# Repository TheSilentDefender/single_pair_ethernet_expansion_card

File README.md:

# single_pair_ethernet_expansion_card

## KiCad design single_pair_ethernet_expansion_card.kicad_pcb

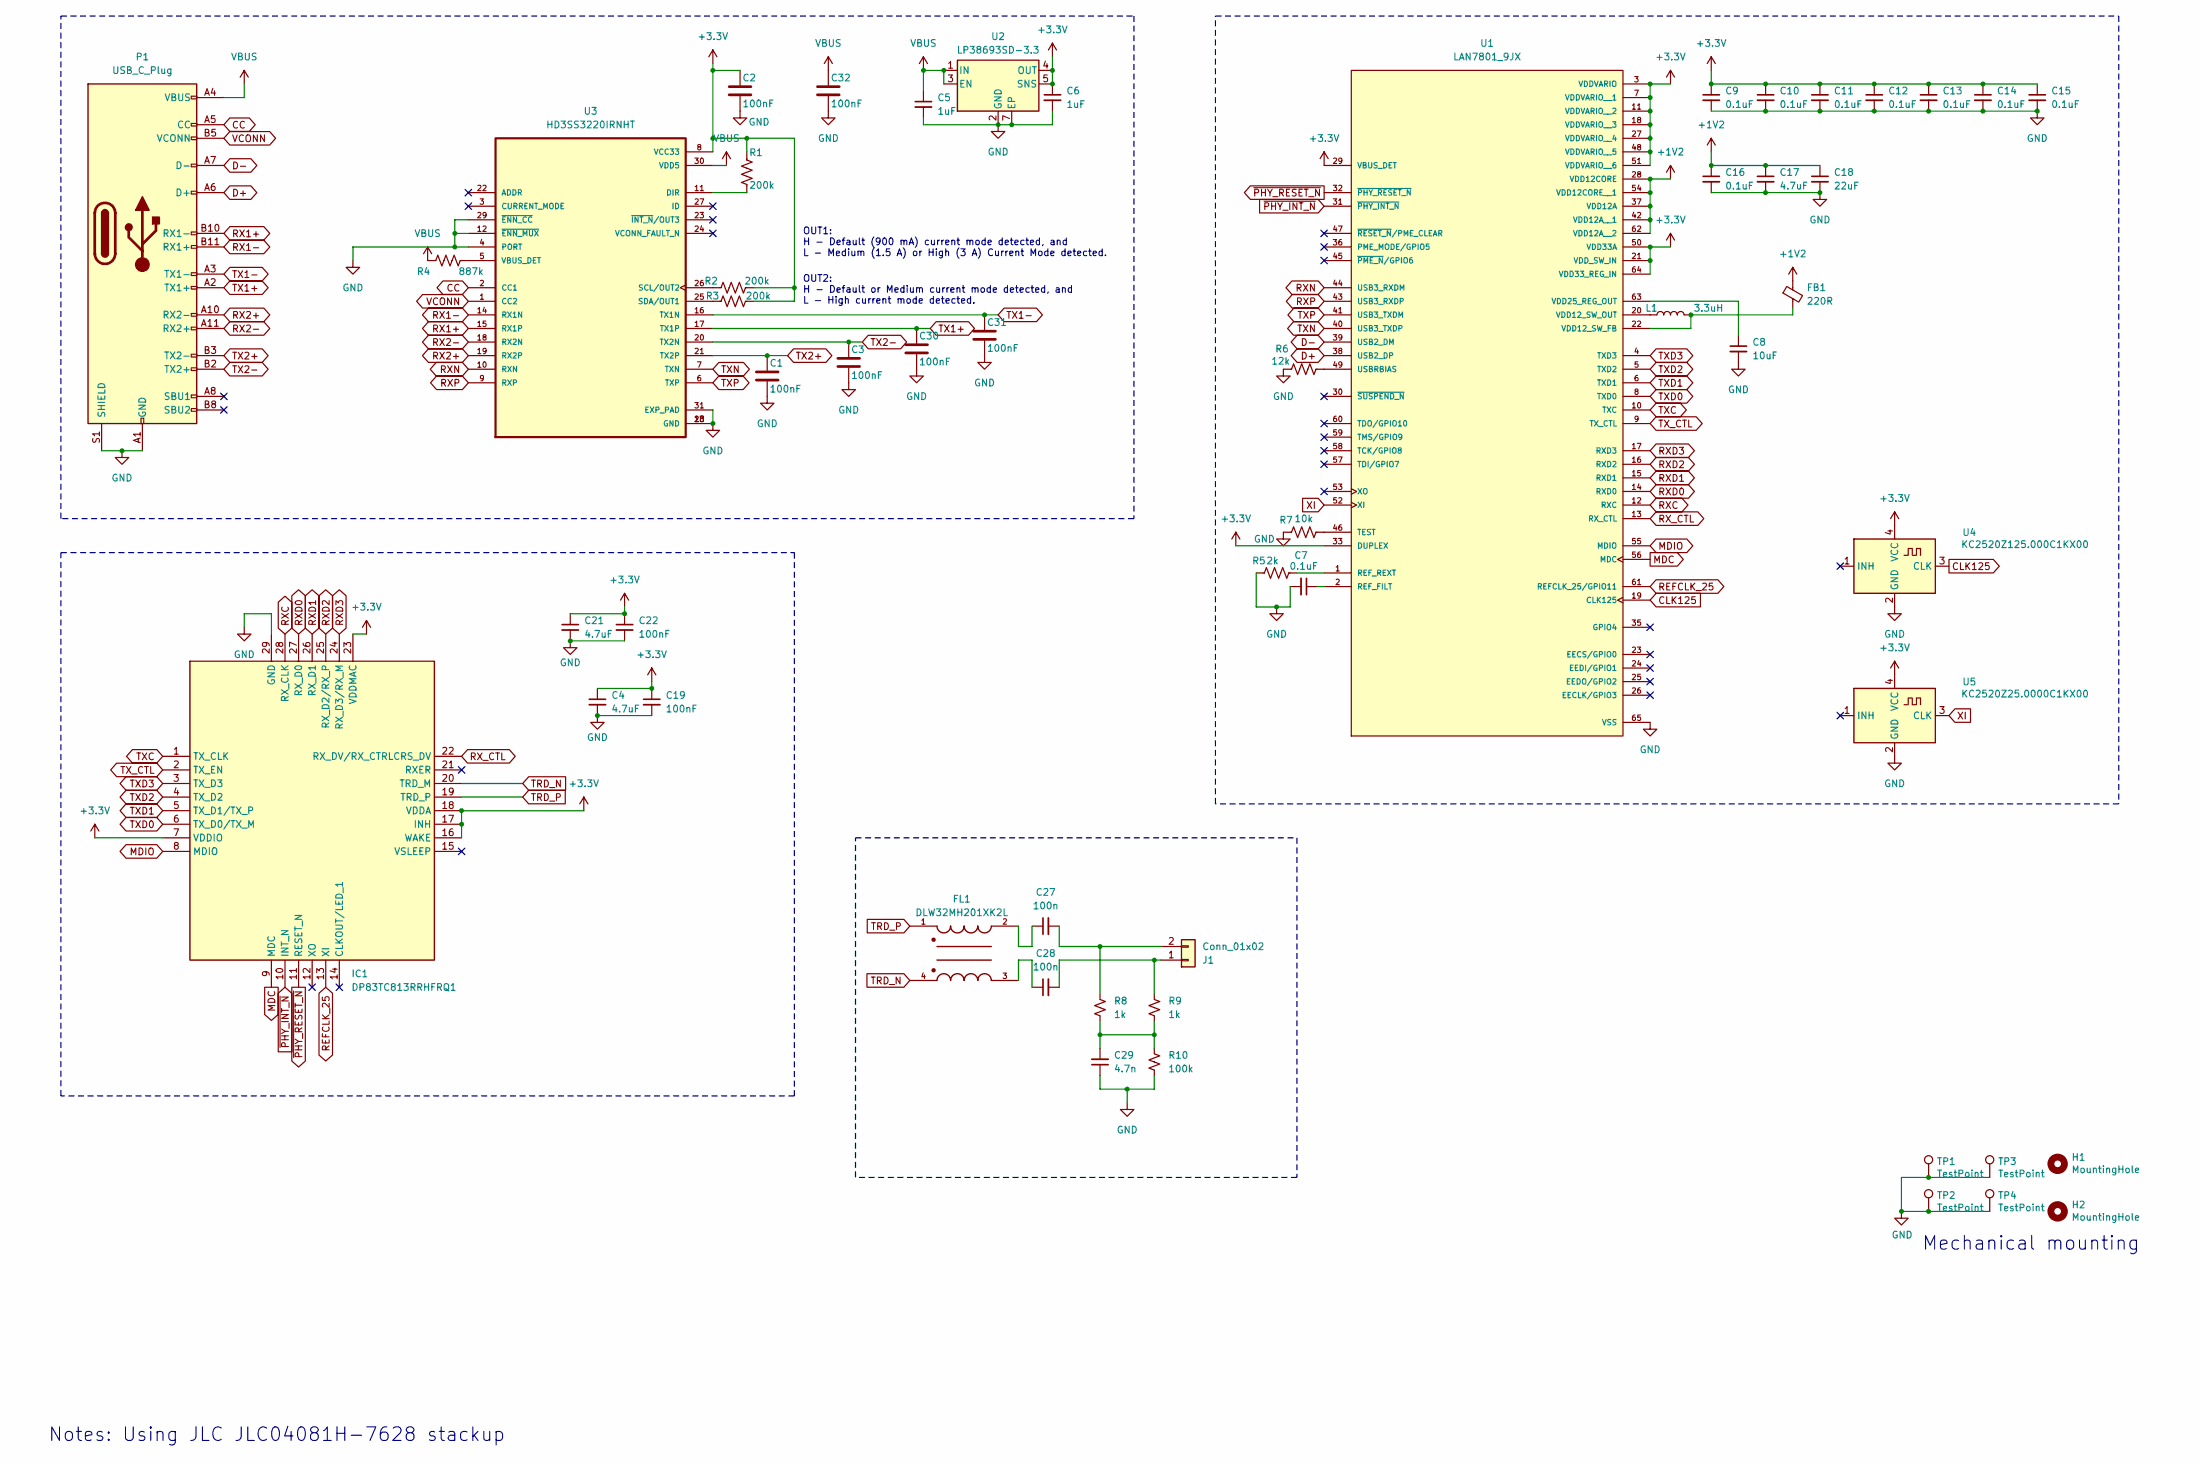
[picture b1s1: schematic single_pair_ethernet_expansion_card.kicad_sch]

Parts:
C1, C2, C3, C30, C31, C32: CC0402KRX5R7BB105; C_0201_0603Metric
C4, C17, C21: 4.7uF; C_0201_0603Metric
C5, C6: 1uF; C_0201_0603Metric
C7, C9, C10, C11, C12, C13, C14, C15, C16: 0.1uF; C_0201_0603Metric
C8: 10uF; C_0201_0603Metric
C18: 22uF; C_0201_0603Metric
C19, C22: 100nF; C_0201_0603Metric
C27, C28: 100n; C_0201_0603Metric
C29: 4.7n; C_0201_0603Metric
FB1: 220R; L_0201_0603Metric
FL1: DLW32MH201XK2L; FIL_DLW32MH201XK2L; PARTREV N/A
H1, H2: MountingHole; MountingHole_2.2mm_M2
IC1: DP83TC813RRHFRQ1; QFN50P400X500X100-29N-D; Mouser Part Number 595-DP83TC813RRHFRQ1
J1: Conn_01x02; JST_SH_SM02B-SRSS-TB_1x02-1MP_P1.00mm_Horizontal
L1: 3.3uH; L_0805_2012Metric
P1: USB_C_Plug; USB_C_Plug_Molex_105444
R1, R2, R3: RC0402JR-07200KL; R_0402_1005Metric
R4: RC0402FR-07887KL; R_0402_1005Metric
R5: 2k; R_0402_1005Metric
R6: 12k; R_0402_1005Metric
R7: 10k; R_0402_1005Metric
R8, R9: 1k; R_0402_1005Metric
R10: 100k; R_0402_1005Metric
TP1, TP2, TP3, TP4: TestPoint; TestPoint_Pad_1.5x1.5mm
U1: LAN7801_9JX; QFN50P900X900X100-65N_LAN7801_9JX; PARTREV DS00002123F
U2: LP38693SD-3.3; WSON-6-1EP_3x3mm_P0.95mm
U3: HD3SS3220IRNHT; QFN40P450X250X80-31N120X320; PART_REV C
U4: KC2520Z125.000C1KX00; Oscillator_SMD_Kyocera_KC2520Z-4Pin_2.5x2.0mm
U5: KC2520Z25.0000C1KX00; Oscillator_SMD_Kyocera_KC2520Z-4Pin_2.5x2.0mm

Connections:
+1V2: C16.1, C17.1, C18.1, FB1.1, U1.28 (VDD12CORE), U1.37 (VDD12A), U1.42 (VDD12A__1), U1.54 (VDD12CORE__1), U1.62 (VDD12A__2)
+3.3V: C2.1, C4.1, C6.1, C9.1, C10.1, C11.1, C12.1, C13.1, C14.1, C15.1, C19.1, C21.1, C22.1, IC1.7 (VDDIO), IC1.16 (WAKE), IC1.17 (INH), IC1.18 (VDDA), IC1.23 (VDDMAC), R1.1, R2.2, R3.2, U1.3 (VDDVARIO), U1.7 (VDDVARIO__1), U1.11 (VDDVARIO__2), U1.18 (VDDVARIO__3), U1.21 (VDD_SW_IN), U1.27 (VDDVARIO__4), U1.29 (VBUS_DET), U1.33 (DUPLEX), U1.48 (VDDVARIO__5), U1.50 (VDD33A), U1.51 (VDDVARIO__6), U1.64 (VDD33_REG_IN), U2.4 (OUT), U2.5 (SNS), U3.8 (VCC33), U4.4 (VCC), U5.4 (VCC)
CC: P1.A5 (CC), U3.2 (CC1)
CLK125: U1.19 (CLK125), U4.3 (CLK)
D+: P1.A6 (D+), U1.38 (USB2_DP)
D-: P1.A7 (D-), U1.39 (USB2_DM)
GND: C1.2, C2.2, C3.2, C4.2, C5.2, C6.2, C7.2, C8.2, C9.2, C10.2, C11.2, C12.2, C13.2, C14.2, C15.2, C16.2, C17.2, C18.2, C19.2, C21.2, C22.2, C29.1, C30.2, C31.2, C32.2, IC1.29 (GND), J1.MP, P1.A1 (GND), P1.A12 (GND), P1.B1 (GND), P1.B12 (GND), P1.S1 (SHIELD), R5.1, R6.1, R7.1, R10.2, TP1.1, TP2.1, TP3.1, TP4.1, U1.65 (VSS), U2.2 (GND), U2.7 (EP), U3.4 (PORT), U3.12 (~ENN_MUX), U3.13 (GND), U3.28 (GND), U3.29 (~ENN_CC), U3.31 (EXP_PAD), U4.2 (GND), U5.2 (GND)
MDC: IC1.9 (MDC), U1.56 (MDC)
MDIO: IC1.8 (MDIO), U1.55 (MDIO)
unnamed: C27.1, FL1.2
unnamed: C28.1, FL1.3
unnamed: C29.2, R8.2, R9.2, R10.1
unnamed: C28.2, J1.1, R9.1
unnamed: C27.2, J1.2, R8.1
unnamed: C7.1, U1.2 (REF_FILT)
unnamed: R5.2, U1.1 (REF_REXT)
unnamed: R7.2, U1.46 (TEST)
unnamed: R6.2, U1.49 (USBRBIAS)
unnamed: FB1.2, L1.2, U1.22 (VDD12_SW_FB)
unnamed: L1.1, U1.20 (VDD12_SW_OUT)
unnamed: C8.1, U1.63 (VDD25_REG_OUT)
unnamed: R1.2, U3.11 (DIR)
unnamed: R2.1, U3.26 (SCL/OUT2)
unnamed: R3.1, U3.25 (SDA/OUT1)
unnamed: R4.2, U3.5 (VBUS_DET)
REFCLK_25: IC1.13 (XI), U1.61 (REFCLK_25/GPIO11)
RX1+: P1.B10 (RX1-), U3.15 (RX1P)
RX1-: P1.B11 (RX1+), U3.14 (RX1N)
RX2+: P1.A10 (RX2-), U3.19 (RX2P)
RX2-: P1.A11 (RX2+), U3.18 (RX2N)
RXC: IC1.28 (RX_CLK), U1.12 (RXC)
RXD0: IC1.27 (RX_D0), U1.14 (RXD0)
RXD1: IC1.26 (RX_D1), U1.15 (RXD1)
RXD2: IC1.25 (RX_D2/RX_P), U1.16 (RXD2)
RXD3: IC1.24 (RX_D3/RX_M), U1.17 (RXD3)
RXN: U1.44 (USB3_RXDM), U3.10 (RXN)
RXP: U1.43 (USB3_RXDP), U3.9 (RXP)
RX_CTL: IC1.22 (RX_DV/RX_CTRLCRS_DV), U1.13 (RX_CTL)
TRD_N: FL1.4, IC1.20 (TRD_M)
TRD_P: FL1.1, IC1.19 (TRD_P)
TX1+: C30.1, P1.A2 (TX1+), U3.17 (TX1P)
TX1-: C31.1, P1.A3 (TX1-), U3.16 (TX1N)
TX2+: C1.1, P1.B3 (TX2-), U3.21 (TX2P)
TX2-: C3.1, P1.B2 (TX2+), U3.20 (TX2N)
TXC: IC1.1 (TX_CLK), U1.10 (TXC)
TXD0: IC1.6 (TX_D0/TX_M), U1.8 (TXD0)
TXD1: IC1.5 (TX_D1/TX_P), U1.6 (TXD1)
TXD2: IC1.4 (TX_D2), U1.5 (TXD2)
TXD3: IC1.3 (TX_D3), U1.4 (TXD3)
TXN: U1.40 (USB3_TXDP), U3.7 (TXN)
TXP: U1.41 (USB3_TXDM), U3.6 (TXP)
TX_CTL: IC1.2 (TX_EN), U1.9 (TX_CTL)
VBUS: C5.1, C32.1, P1.A4 (VBUS), P1.A9 (VBUS), P1.B4 (VBUS), P1.B9 (VBUS), R4.1, U2.1 (IN), U2.3 (EN), U2.6 (IN), U3.30 (VDD5)
VCONN: P1.B5 (VCONN), U3.1 (CC2)
XI: U1.52 (XI), U5.3 (CLK)
~PHY_INT_N: IC1.10 (INT_N), U1.31 (~PHY_INT_N)
~PHY_RESET_N: IC1.11 (RESET_N), U1.32 (~PHY_RESET_N)

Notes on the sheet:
OUT2: H - Default or Medium current mode detected, and L - High current mode detected.
Notes: Using JLC JLC04081H-7628 stackup
Mechanical mounting
OUT1: H - Default (900 mA) current mode detected, and L - Medium (1.5 A) or High (3 A) Current Mode detected.

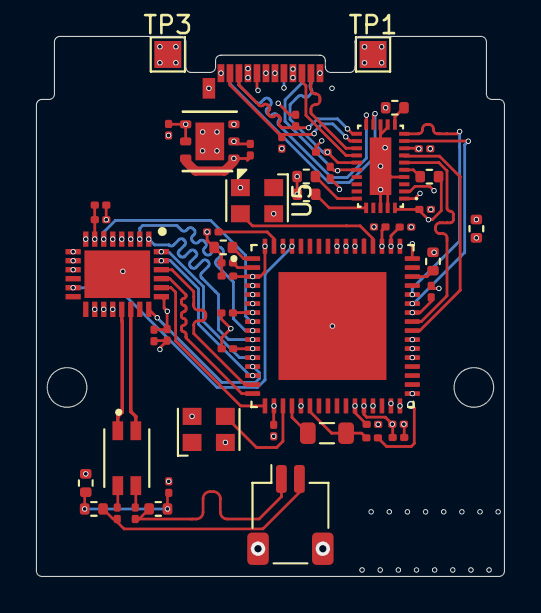
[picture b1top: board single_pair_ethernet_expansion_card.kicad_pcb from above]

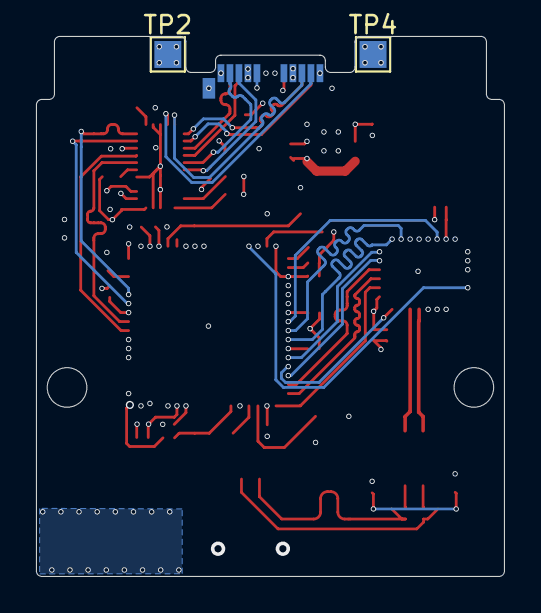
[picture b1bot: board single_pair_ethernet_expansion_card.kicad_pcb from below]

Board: 4 copper layers, 26.0 x 30.0 mm, 54 parts (2 on the bottom side), 57 nets.

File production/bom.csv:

Designator,Footprint,Quantity,Value,LCSC Part #
"C1, C2, C3, C30, C31, C32",0201,6,CC0402KRX5R7BB105,
"C10, C11, C12, C13, C14, C15, C16, C7, C9",0201,9,0.1uF,
"C17, C21, C4",0201,3,4.7uF,
C18,0201,1,22uF,
"C19, C22",0201,2,100nF,
"C27, C28",0201,2,100n,
C29,0201,1,4.7n,
"C5, C6",0201,2,1uF,
C8,0201,1,10uF,
FB1,0201,1,220R,
FL1,FIL_DLW32MH201XK2L,1,DLW32MH201XK2L,
"H1, H2",MountingHole_2.2mm_M2,2,MountingHole,
IC1,QFN50P400X500X100-29N-D,1,DP83TC813RRHFRQ1,
J1,JST_SH_SM02B-SRSS-TB_1x02-1MP_P1.00mm_Horizontal,1,Conn_01x02,
L1,0805,1,3.3uH,
P1,USB_C_Plug_Molex_105444,1,USB_C_Plug,
"R1, R2, R3",0402,3,RC0402JR-07200KL,
R10,0402,1,100k,
R4,0402,1,RC0402FR-07887KL,
R5,0402,1,2k,
R6,0402,1,12k,
R7,0402,1,10k,
"R8, R9",0402,2,1k,
"TP1, TP2, TP3, TP4",TestPoint_Pad_1.5x1.5mm,4,TestPoint,
U1,QFN50P900X900X100-65N_LAN7801_9JX,1,LAN7801_9JX,
U2,WSON-6-1EP_3x3mm_P0.95mm,1,LP38693SD-3.3,
U3,QFN40P450X250X80-31N120X320,1,HD3SS3220IRNHT,
U4,Oscillator_SMD_Kyocera_KC2520Z-4Pin_2.5x2.0mm,1,KC2520Z125.000C1KX00,
U5,Oscillator_SMD_Kyocera_KC2520Z-4Pin_2.5x2.0mm,1,KC2520Z25.0000C1KX00,

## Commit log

2025-02-26 fixed impedence

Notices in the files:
single_pair_ethernet_expansion_card.kicad_pcb:
This work is licensed under a Creative Commons Attribution 4.0 International License
